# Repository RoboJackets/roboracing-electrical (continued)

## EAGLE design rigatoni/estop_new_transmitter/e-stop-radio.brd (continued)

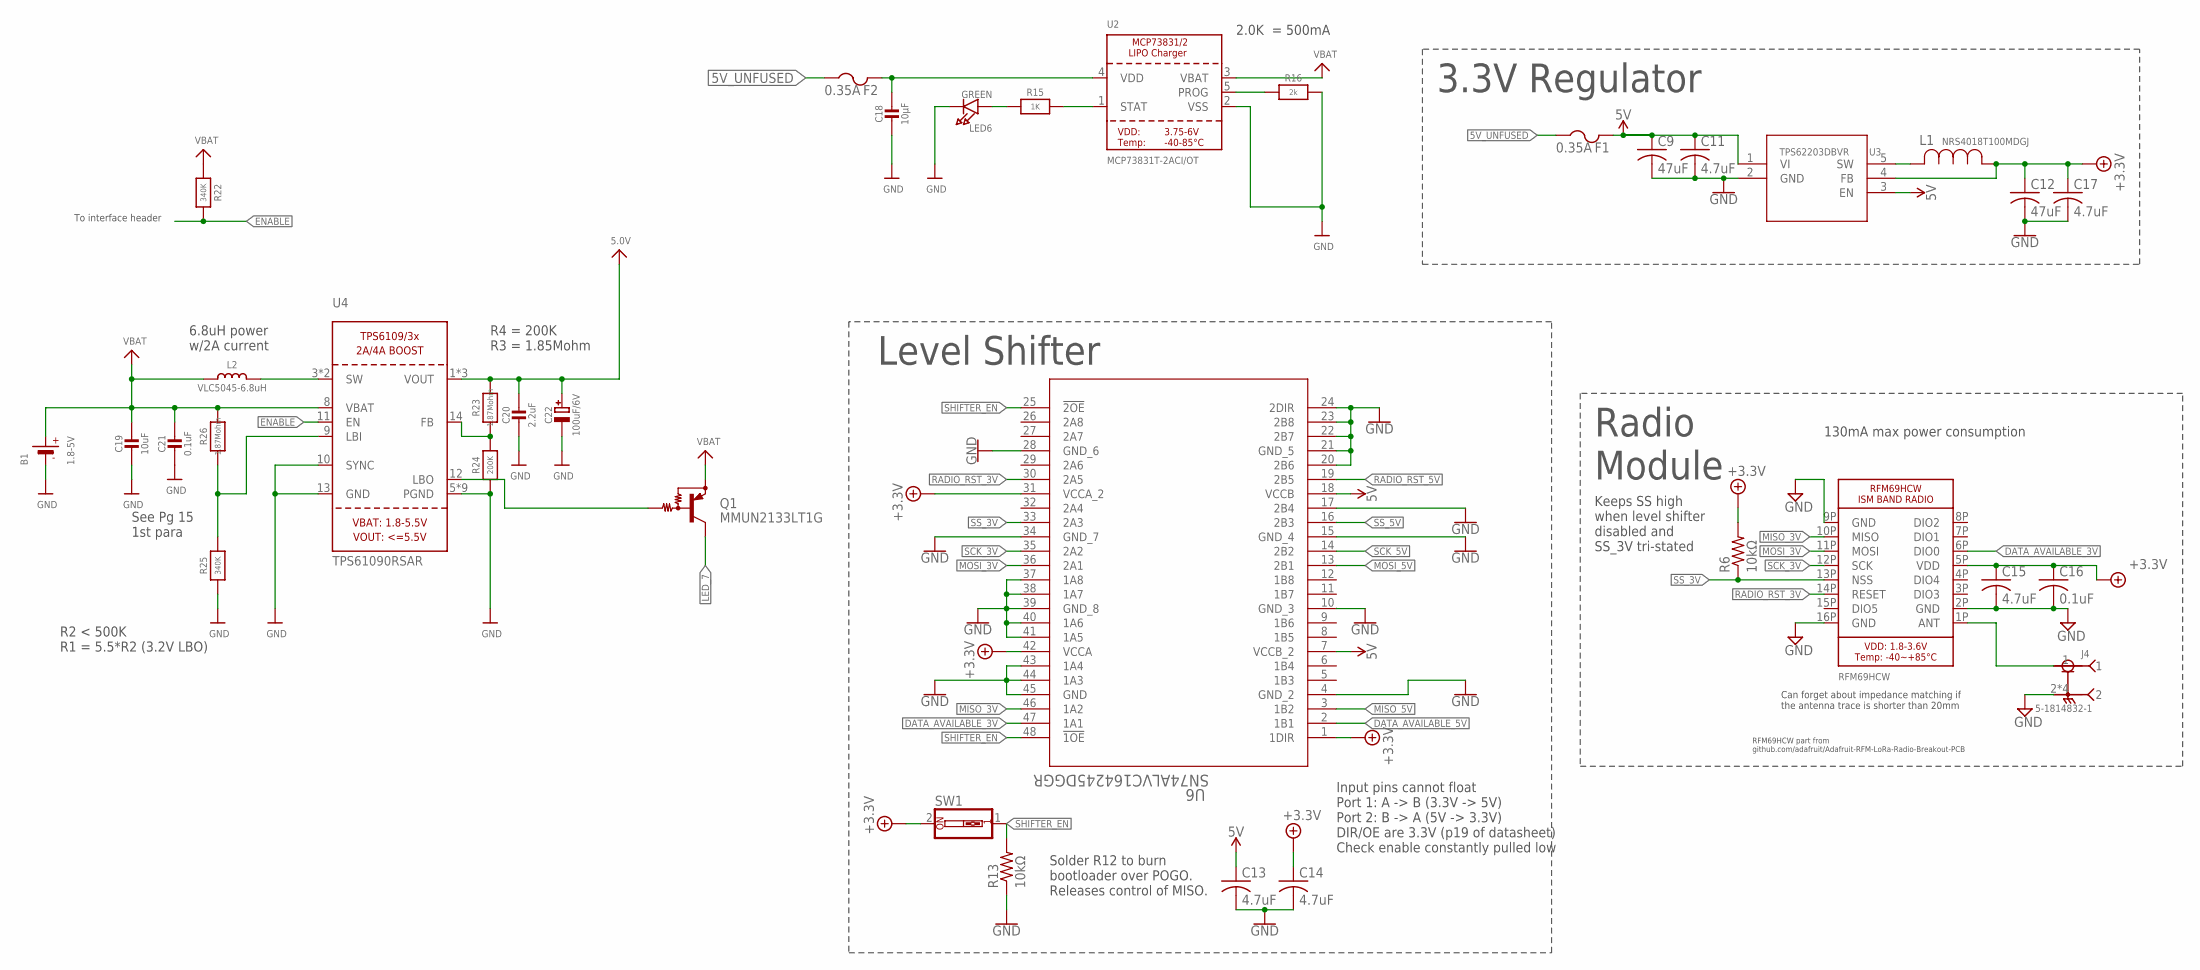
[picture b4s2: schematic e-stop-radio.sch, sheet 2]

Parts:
B1: 1.8-5V; JSTPH2
C9, C12: 47uF; C1206
C11, C13, C14, C15, C17: 4.7uF; C0603
C16: 0.1uF; C0603
C18: 10µF; 0805-NO
C19: 10uF; 0805-NO
C20: 2.2uF; 0805-NO
C21: 0.1uF; 0805-NO
C22: 100uF/6V; EIA3528-21/B-R
F1, F2: 0.35A; R1206
J4: 5-1814832-1; TE_5-1814832-1
L1: NRS4018T100MDGJ; IND_TAIYO_NRS4018
L2: VLC5045-6.8uH; INDUCTOR_5X5MM_TDK_VLC5045
LED6: GREEN; CHIPLED_0805_NOOUTLINE
Q1: MMUN2133LT1G; SC59-BEC
R6, R13: 10kΩ; R0603
R15: 1K; 0805-NO
R16: 2k; 0805-NO
R22, R25: 340K; 0805-NO
R23, R26: 1.87Mohm; 0805-NO
R24: 200K; 0805-NO
SW1: SW_DIP-1; EDG-01
U2: MCP73831T-2ACI/OT; SOT23-5
U3: TPS62203DBVR; DBV5
U4: TPS61090RSAR; PVQFN-16
U5: RFM69HCW; RFMHCW_SMT
U6: SN74ALVC164245DGGR; DGG48

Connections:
5V: C9.1, C11.1, C13.1, C20.1, C22.+, F1.2, R23.2, U3.1 (VI), U3.3 (EN), U4.1 (VOUT), U4.15 (VOUT), U4.16 (VOUT), U6.7 (VCCB_2), U6.18 (VCCB); also elsewhere on the board
5V_UNFUSED: F1.1, F2.1; also elsewhere on the board
+3.3V: C12.1, C14.1, C15.1, C16.1, C17.1, L1.1, R6.2, SW1.2, U3.4 (FB), U5.5P (VDD), U6.1 (1DIR), U6.31 (VCCA_2), U6.42 (VCCA); also elsewhere on the board
CHARGER: C18.1, F2.2, U2.4 (VDD)
DATA_AVAILABLE_3V: U5.6P (DIO0), U6.47 (1A1)
DATA_AVAILABLE_5V: U6.2 (1B1); also elsewhere on the board
ENABLE: R22.2, U4.11 (EN); also elsewhere on the board
GND: B1.1 (-), C9.2, C11.2, C12.2, C13.2, C14.2, C15.2, C16.2, C17.2, C18.2, C19.2, C20.2, C21.2, C22.-, J4.2, J4.3 (2), J4.4 (2), J4.5 (2), LED6.C, R13.1, R16.2, R24.1, R25.1, U2.2 (VSS), U3.2 (GND), U4.5 (PGND), U4.6 (PGND), U4.7 (PGND), U4.10 (SYNC), U4.13 (GND), U4.P$18 (PGND), U4.P$19 (PGND), U4.P$20 (PGND), U4.P$21 (PGND), U4.P$22 (PGND), U4.THERMAL (PGND), U5.2P (GND), U5.9P (GND), U5.16P (GND), U6.4 (GND_2), U6.10 (GND_3), U6.15 (GND_4), U6.17 (2B4), U6.20 (2B6), U6.21 (GND_5), U6.22 (2B7), U6.23 (2B8), U6.24 (2DIR), U6.28 (GND_6), U6.34 (GND_7), U6.37 (1A8), U6.38 (1A7), U6.39 (GND_8), U6.40 (1A6), U6.41 (1A5), U6.43 (1A4), U6.44 (1A3), U6.45 (GND); also elsewhere on the board
LBO: Q1.B, U4.12 (LBO)
LED_7: Q1.C; also elsewhere on the board
MISO_3V: U5.10P (MISO), U6.46 (1A2)
MISO_5V: U6.3 (1B2); also elsewhere on the board
MOSI_3V: U5.11P (MOSI), U6.36 (2A1)
MOSI_5V: U6.13 (2B1); also elsewhere on the board
unnamed: L1.2, U3.5 (SW)
unnamed: R15.2, U2.1 (STAT)
unnamed: R16.1, U2.5 (PROG)
unnamed: LED6.A, R15.1
unnamed: L2.P$2 (2), U4.3 (SW), U4.4 (SW)
unnamed: R25.2, R26.1, U4.9 (LBI)
unnamed: R23.1, R24.2, U4.14 (FB)
RADIO_RST_3V: U5.14P (RESET), U6.30 (2A5)
RADIO_RST_5V: U6.19 (2B5); also elsewhere on the board
RF_SIGNAL: J4.1, U5.1P (ANT)
SCK_3V: U5.12P (SCK), U6.35 (2A2)
SCK_5V: U6.14 (2B2); also elsewhere on the board
SHIFTER_EN: R13.2, SW1.1, U6.25 (!2OE), U6.48 (!1OE)
SS_3V: R6.1, U5.13P (NSS), U6.33 (2A3)
SS_5V: U6.16 (2B3); also elsewhere on the board
VBAT: B1.2 (+), C19.1, C21.1, L2.P$1 (1), Q1.E, R22.1, R26.2, U2.3 (VBAT), U4.8 (VBAT)

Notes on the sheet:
RFM69HCW part from github.com/adafruit/Adafruit-RFM-LoRa-Radio-Breakout-PCB
130mA max power consumption
Radio Module
Can forget about impedance matching if the antenna trace is shorter than 20mm
3.3V Regulator
Level Shifter
Solder R12 to burn bootloader over POGO. Releases control of MISO.
Input pins cannot float Port 1: A -> B (3.3V -> 5V) Port 2: B -> A (5V -> 3.3V) DIR/OE are 3.3V (p19 of datasheet) Check enable constantly pulled low
Keeps SS high when level shifter disabled and SS_3V tri-stated
2.0K = 500mA
See Pg 15 1st para
6.8uH power w/2A current
R2 < 500K R1 = 5.5*R2 (3.2V LBO)
R4 = 200K R3 = 1.85Mohm
To interface header

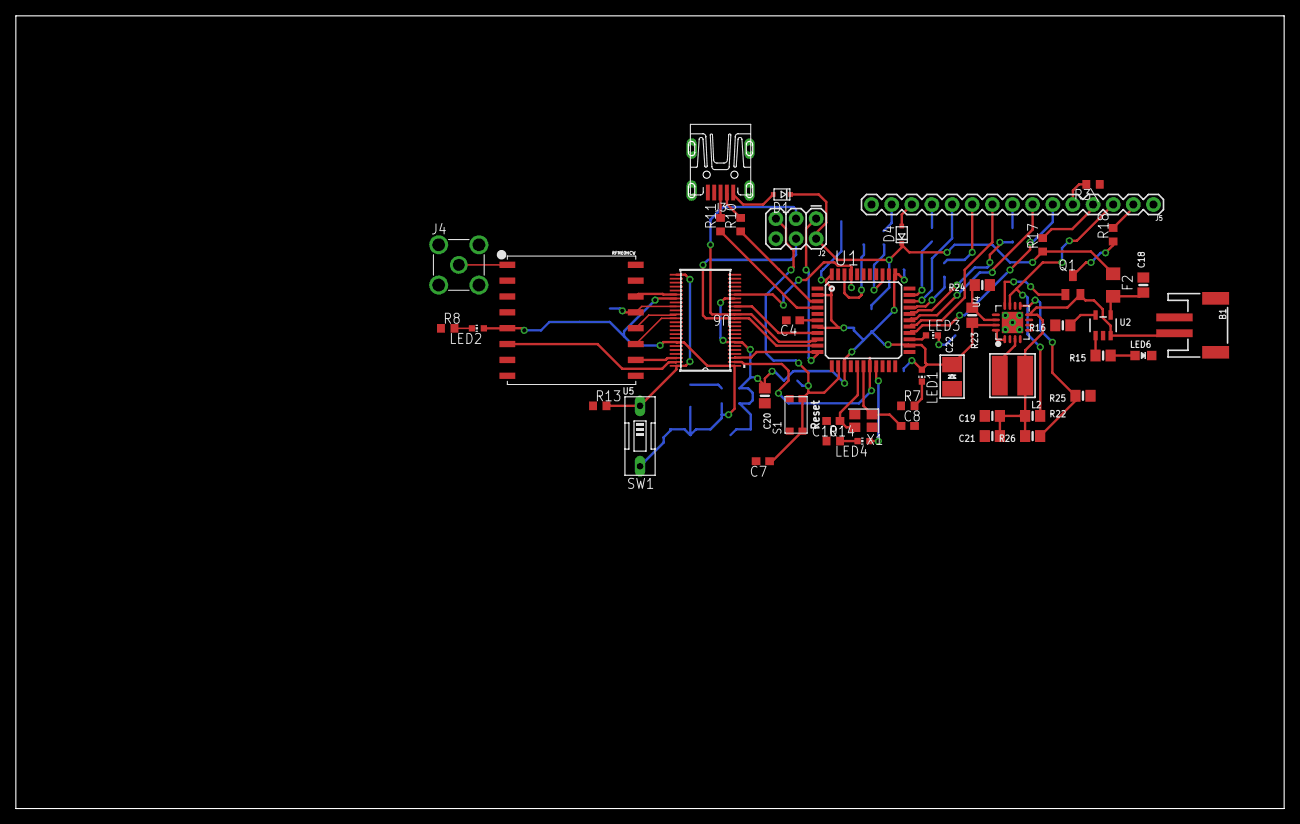
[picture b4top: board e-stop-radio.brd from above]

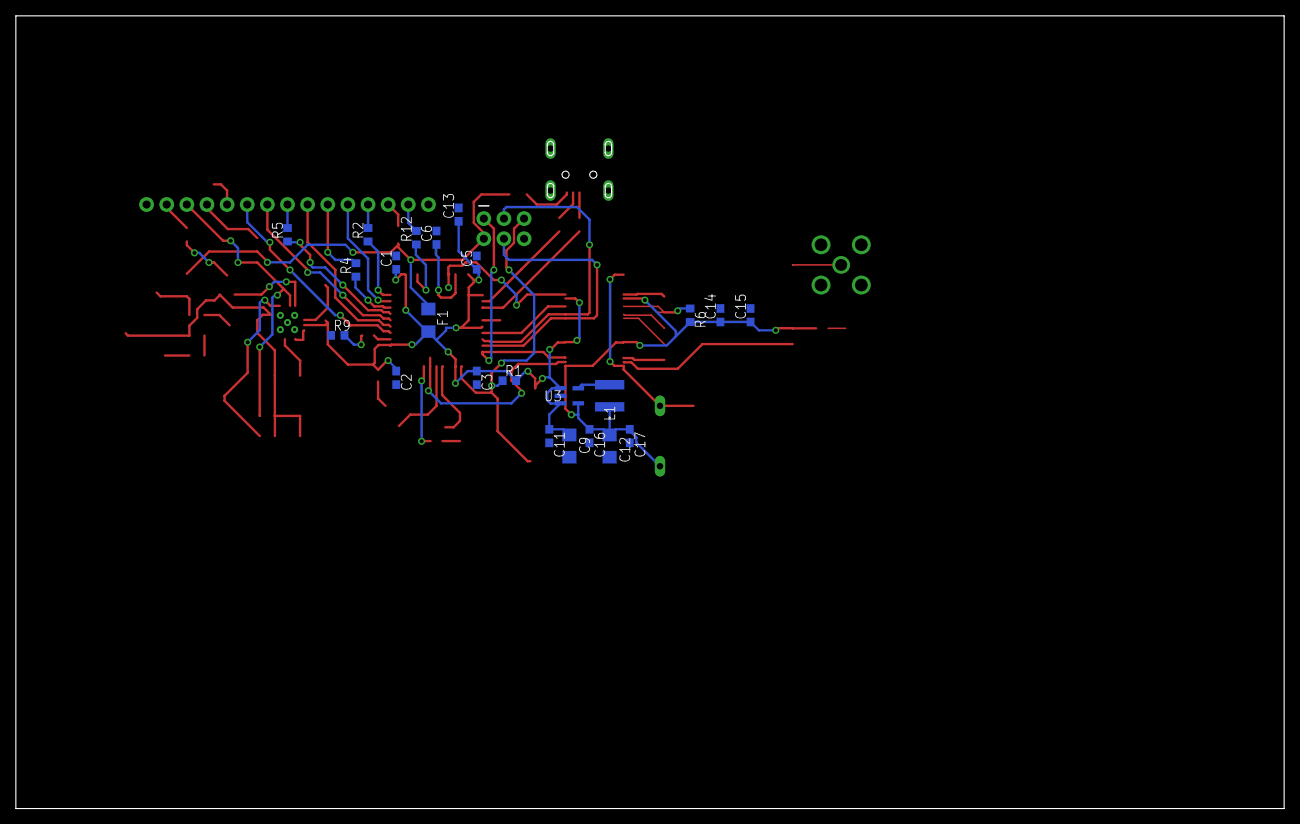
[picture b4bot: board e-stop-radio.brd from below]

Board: 2 copper layers, 160.0 x 100.0 mm, 71 parts (23 on the bottom side), 62 nets.

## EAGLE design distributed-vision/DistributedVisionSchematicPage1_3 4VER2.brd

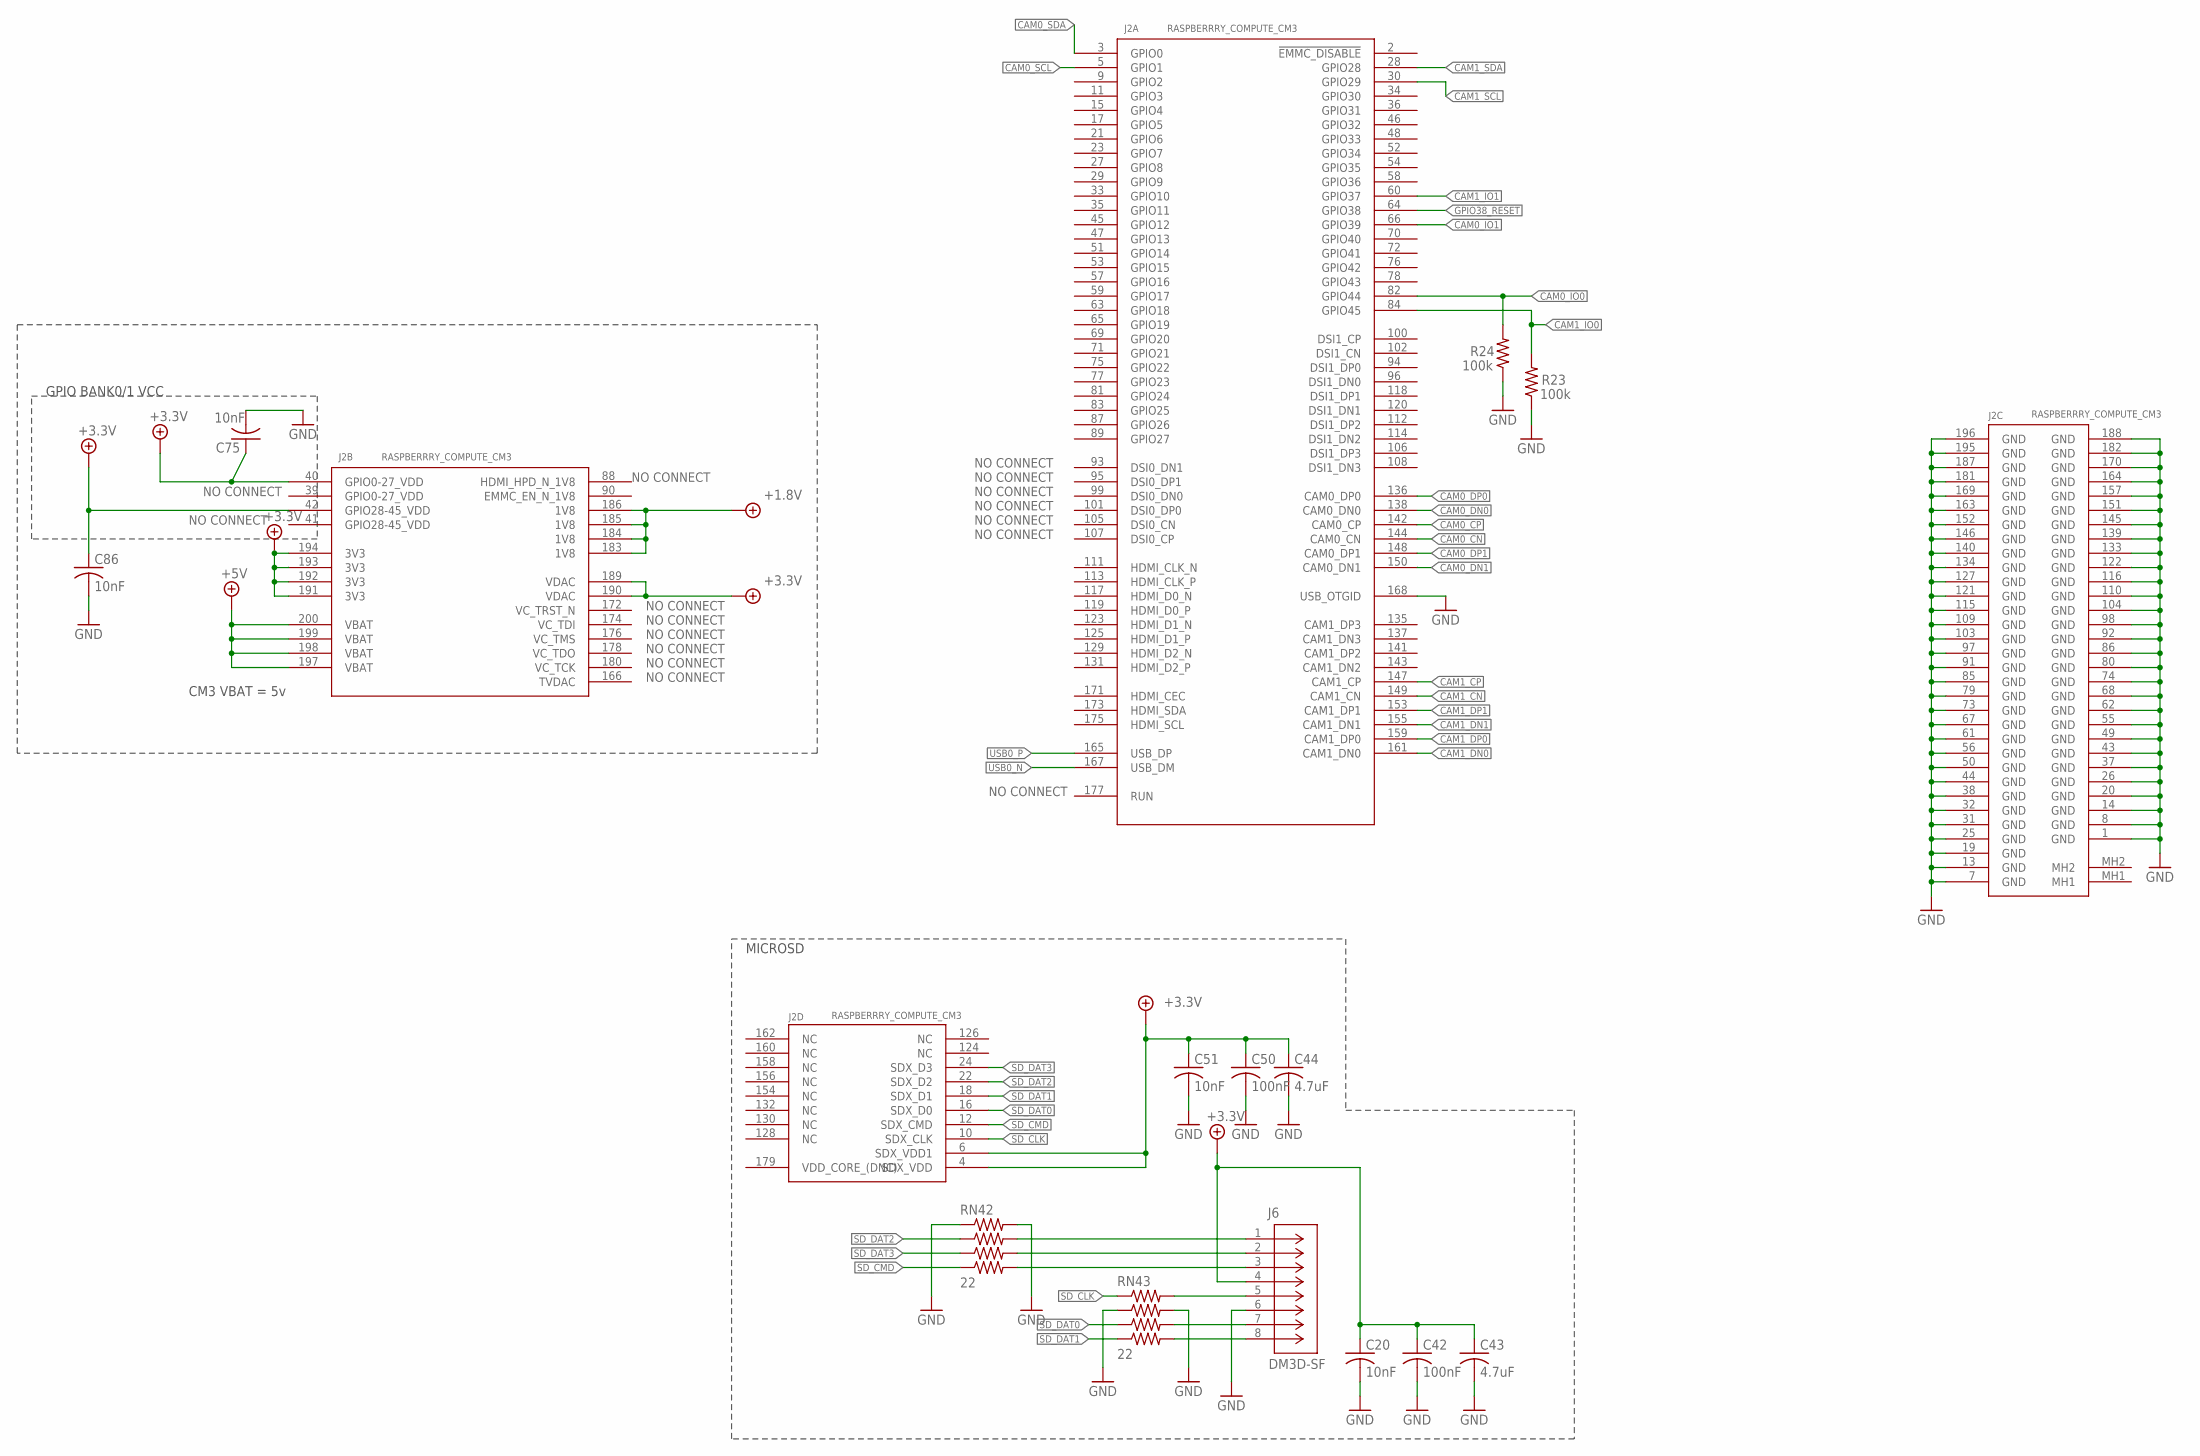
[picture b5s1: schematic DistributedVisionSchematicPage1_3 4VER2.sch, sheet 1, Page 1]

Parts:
C20, C51, C75, C86: 10nF; C0603
C42, C50: 100nF; C0603
C43, C44: 4.7uF; C0603
J2: RASPBERRRY_COMPUTE_CM3; TE_1473149-4_WITH_CM3PLUS
J6: DM3D-SF; CONN8_DM3D-SF_HIR
R23, R24: 100k; R0603
RN42, RN43: 22; RA-4_1206

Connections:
+1.8V: J2.183 (1V8), J2.184 (1V8), J2.185 (1V8), J2.186 (1V8); also elsewhere on the board
+3.3V: C20.1, C42.1, C43.1, C44.1, C50.1, C51.1, C75.1, C86.1, J2.4 (SDX_VDD), J2.6 (SDX_VDD1), J2.40 (GPIO0-27_VDD), J2.42 (GPIO28-45_VDD), J2.189 (VDAC), J2.190 (VDAC), J2.191 (3V3), J2.192 (3V3), J2.193 (3V3), J2.194 (3V3), J6.4; also elsewhere on the board
+5V: J2.197 (VBAT), J2.198 (VBAT), J2.199 (VBAT), J2.200 (VBAT); also elsewhere on the board
CAM0_CN: J2.144 (CAM0_CN); also elsewhere on the board
CAM0_CP: J2.142 (CAM0_CP); also elsewhere on the board
CAM0_DN0: J2.138 (CAM0_DN0); also elsewhere on the board
CAM0_DN1: J2.150 (CAM0_DN1); also elsewhere on the board
CAM0_DP0: J2.136 (CAM0_DP0); also elsewhere on the board
CAM0_DP1: J2.148 (CAM0_DP1); also elsewhere on the board
CAM0_IO0: J2.82 (GPIO44), R24.2; also elsewhere on the board
CAM0_IO1: J2.66 (GPIO39); also elsewhere on the board
CAM0_SCL: J2.5 (GPIO1); also elsewhere on the board
CAM0_SDA: J2.3 (GPIO0); also elsewhere on the board
CAM1_CN: J2.149 (CAM1_CN); also elsewhere on the board
CAM1_CP: J2.147 (CAM1_CP); also elsewhere on the board
CAM1_DN0: J2.161 (CAM1_DN0); also elsewhere on the board
CAM1_DN1: J2.155 (CAM1_DN1); also elsewhere on the board
CAM1_DP0: J2.159 (CAM1_DP0); also elsewhere on the board
CAM1_DP1: J2.153 (CAM1_DP1); also elsewhere on the board
CAM1_IO0: J2.84 (GPIO45), R23.2; also elsewhere on the board
CAM1_IO1: J2.60 (GPIO37); also elsewhere on the board
CAM1_SCL: J2.30 (GPIO29); also elsewhere on the board
CAM1_SDA: J2.28 (GPIO28); also elsewhere on the board
GND: C20.2, C42.2, C43.2, C44.2, C50.2, C51.2, C75.2, C86.2, J2.1 (GND), J2.7 (GND), J2.8 (GND), J2.13 (GND), J2.14 (GND), J2.19 (GND), J2.20 (GND), J2.25 (GND), J2.26 (GND), J2.31 (GND), J2.32 (GND), J2.37 (GND), J2.38 (GND), J2.43 (GND), J2.44 (GND), J2.49 (GND), J2.50 (GND), J2.55 (GND), J2.56 (GND), J2.61 (GND), J2.62 (GND), J2.67 (GND), J2.68 (GND), J2.73 (GND), J2.74 (GND), J2.79 (GND), J2.80 (GND), J2.85 (GND), J2.86 (GND), J2.91 (GND), J2.92 (GND), J2.97 (GND), J2.98 (GND), J2.103 (GND), J2.104 (GND), J2.109 (GND), J2.110 (GND), J2.115 (GND), J2.116 (GND), J2.121 (GND), J2.122 (GND), J2.127 (GND), J2.133 (GND), J2.134 (GND), J2.139 (GND), J2.140 (GND), J2.145 (GND), J2.146 (GND), J2.151 (GND), J2.152 (GND), J2.157 (GND), J2.163 (GND), J2.164 (GND), J2.168 (USB_OTGID), J2.169 (GND), J2.170 (GND), J2.181 (GND), J2.182 (GND), J2.187 (GND), J2.188 (GND), J2.195 (GND), J2.196 (GND), J6.6, R23.1, R24.1, RN42.1, RN42.2, RN43.3, RN43.4; also elsewhere on the board
GPIO0-27_VDD: J2.39 (GPIO0-27_VDD)
GPIO28-45_VDD: J2.41 (GPIO28-45_VDD)
GPIO38_RESET: J2.64 (GPIO38)
unnamed: J6.1, RN42.4
unnamed: J6.2, RN42.6
unnamed: J6.3, RN42.8
unnamed: J6.5, RN43.2
unnamed: J6.7, RN43.6
unnamed: J6.8, RN43.8
SD_CLK: J2.10 (SDX_CLK), RN43.1
SD_CMD: J2.12 (SDX_CMD), RN42.7
SD_DAT0: J2.16 (SDX_D0), RN43.5
SD_DAT1: J2.18 (SDX_D1), RN43.7
SD_DAT2: J2.22 (SDX_D2), RN42.3
SD_DAT3: J2.24 (SDX_D3), RN42.5
USB0_N: J2.167 (USB_DM); also elsewhere on the board
USB0_P: J2.165 (USB_DP); also elsewhere on the board
VC_TCK: J2.180 (VC_TCK)
VC_TDO: J2.178 (VC_TDO)

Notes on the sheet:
MICROSD
NO CONNECT
GPIO BANK0/1 VCC
CM3 VBAT = 5v

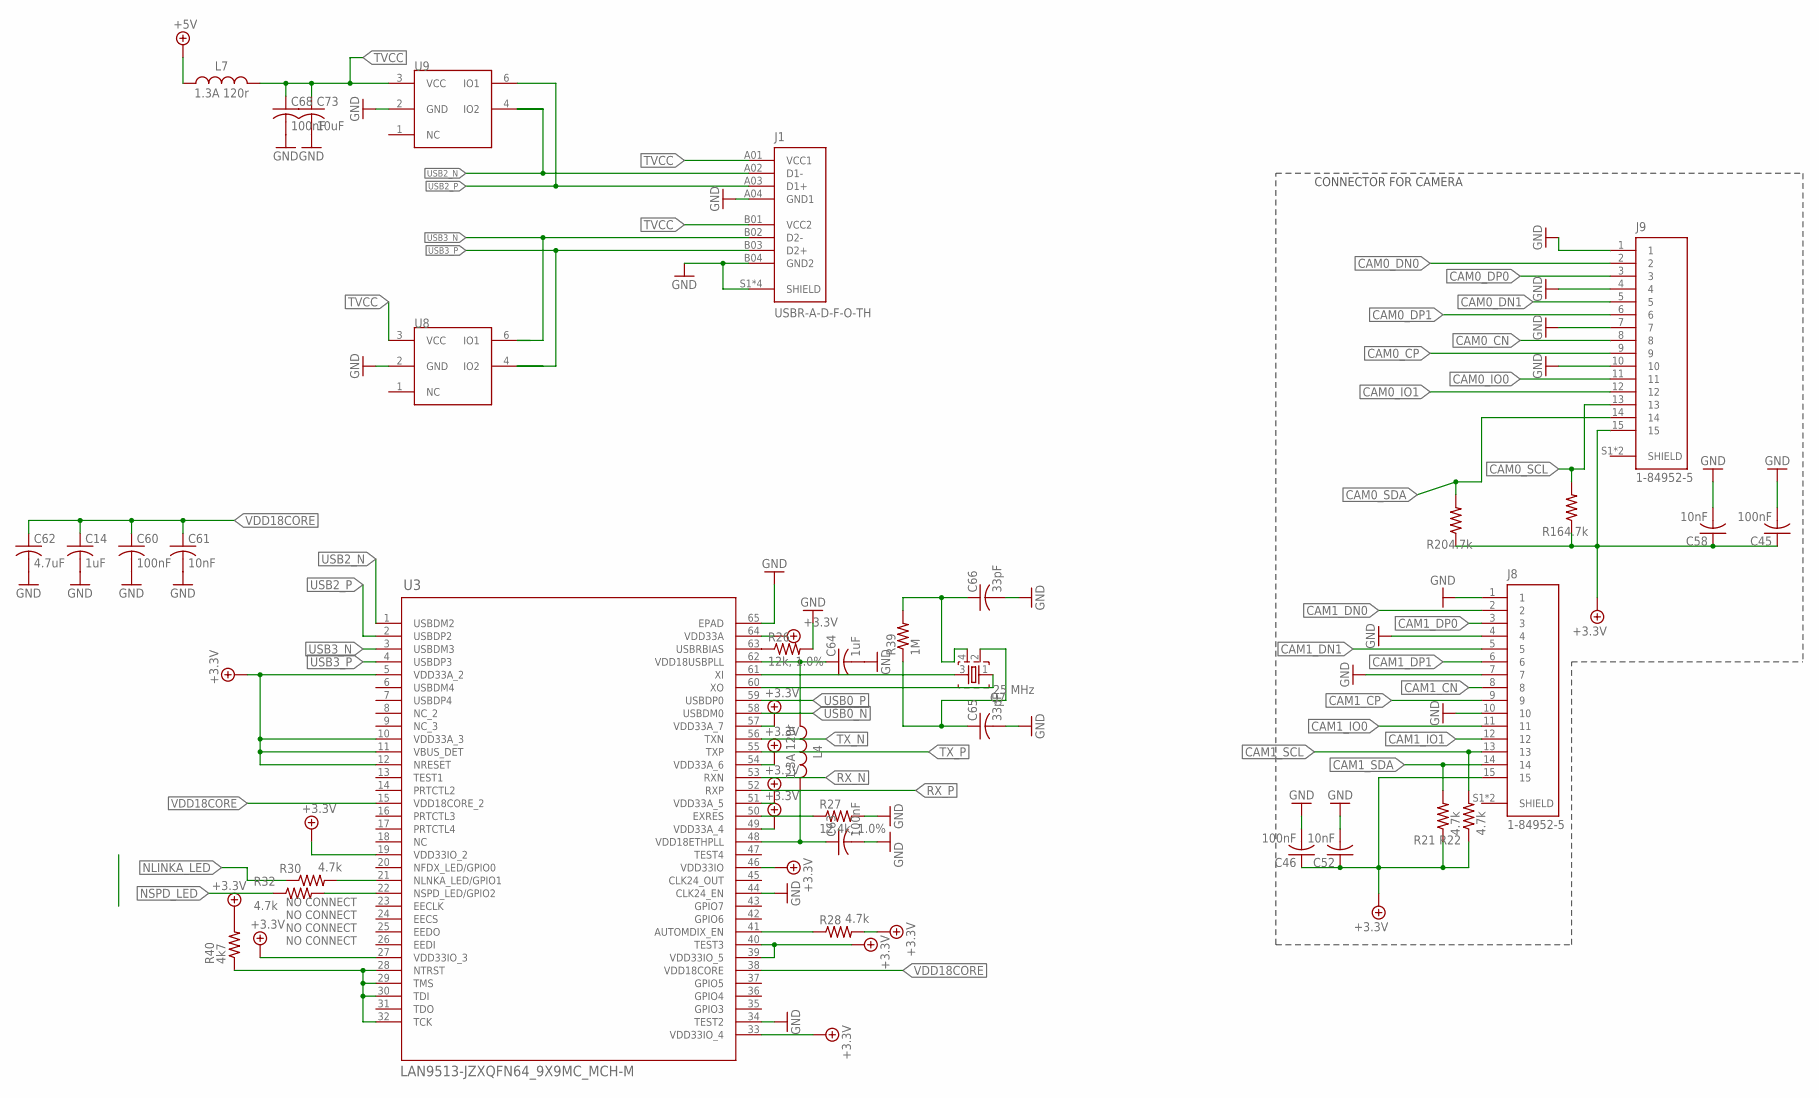
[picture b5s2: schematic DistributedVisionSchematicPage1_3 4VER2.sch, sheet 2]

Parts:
C14, C64: 1uF; C0402
C45, C46: 100nF; C0603
C52, C58: 10nF; C0603
C60, C63, C68: 100nF; C0402
C61: 10nF; C0402
C62: 4.7uF; C0402
C65, C66: 33pF; C0402
C73: 10uF; C0402
J1: USBR-A-D-F-O-TH; SAMTEC_USBR-A-D-F-O-TH
J8, J9: 1-84952-5; TE_1-84952-5
L4, L7: 1.3A 120r; 0805
Q7: 25 MHz; FA-20H
R16, R20, R21, R22: 4.7k; R0603
R26: 12k, 1.0%; RC0805N
R27: 12.4k, 1.0%; RC0805N
R28, R30, R32: 4.7k; RC0805N
R39: 1M; RC0805N
R40: 4k7; RC0805N
U3: LAN9513-JZXQFN64_9X9MC_MCH-M; QFN64_9X9MC_MCH-M
U8, U9: SP3003-02; SC70-5

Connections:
+3.3V: C45.1, C46.1, C52.1, C58.1, J8.15, J9.15, R16.1, R20.1, R21.1, R22.1, R28.2 (PIN2), R40.2 (PIN2), U3.5 (VDD33A_2), U3.10 (VDD33A_3), U3.11 (VBUS_DET), U3.12 (NRESET), U3.19 (VDD33IO_2), U3.27 (VDD33IO_3), U3.33 (VDD33IO_4), U3.39 (VDD33IO_5), U3.40 (TEST3), U3.46 (VDD33IO), U3.49 (VDD33A_4), U3.51 (VDD33A_5), U3.54 (VDD33A_6), U3.57 (VDD33A_7), U3.64 (VDD33A); also elsewhere on the board
+5V: L7.1; also elsewhere on the board
CAM0_CN: J9.8; also elsewhere on the board
CAM0_CP: J9.9; also elsewhere on the board
CAM0_DN0: J9.2; also elsewhere on the board
CAM0_DN1: J9.5; also elsewhere on the board
CAM0_DP0: J9.3; also elsewhere on the board
CAM0_DP1: J9.6; also elsewhere on the board
CAM0_IO0: J9.11; also elsewhere on the board
CAM0_IO1: J9.12; also elsewhere on the board
CAM0_SCL: J9.13, R16.2; also elsewhere on the board
CAM0_SDA: J9.14, R20.2; also elsewhere on the board
CAM1_CN: J8.8; also elsewhere on the board
CAM1_CP: J8.9; also elsewhere on the board
CAM1_DN0: J8.2; also elsewhere on the board
CAM1_DN1: J8.5; also elsewhere on the board
CAM1_DP0: J8.3; also elsewhere on the board
CAM1_DP1: J8.6; also elsewhere on the board
CAM1_IO0: J8.11; also elsewhere on the board
CAM1_IO1: J8.12; also elsewhere on the board
CAM1_SCL: J8.13, R22.2; also elsewhere on the board
CAM1_SDA: J8.14, R21.2; also elsewhere on the board
GND: C14.2, C45.2, C46.2, C52.2, C58.2, C60.2, C61.2, C62.2, C63.2, C64.2, C65.2, C66.2, C68.2, C73.2, J1.A04 (GND1), J1.B04 (GND2), J1.S1 (SHIELD), J1.S2 (SHIELD), J1.S3 (SHIELD), J1.S4 (SHIELD), J8.1, J8.4, J8.7, J8.10, J9.1, J9.4, J9.7, J9.10, R26.2 (PIN2), R27.2 (PIN2), U3.34 (TEST2), U3.44 (CLK24_EN), U3.65 (EPAD), U8.2 (GND), U9.2 (GND); also elsewhere on the board
unnamed: C64.1, L4.1, U3.62 (VDD18USBPLL)
unnamed: C63.1, L4.2, U3.48 (VDD18ETHPLL)
unnamed: R30.2 (PIN2), U3.21 (NLNKA_LED/GPIO1)
unnamed: R32.2 (PIN2), U3.22 (NSPD_LED/GPIO2)
unnamed: R40.1 (PIN1), U3.28 (NTRST), U3.29 (TMS), U3.30 (TDI), U3.32 (TCK)
unnamed: Q7.3, U3.61 (XI)
unnamed: Q7.1, U3.60 (XO)
unnamed: C66.1, Q7.4, R39.2 (PIN2)
unnamed: C65.1, Q7.2, R39.1 (PIN1)
unnamed: R26.1 (PIN1), U3.63 (USBRBIAS)
unnamed: R28.1 (PIN1), U3.41 (AUTOMDIX_EN)
unnamed: R27.1 (PIN1), U3.50 (EXRES)
NLINKA_LED: R30.1 (PIN1)
NSPD_LED: R32.1 (PIN1)
RX_N: U3.53 (RXN); also elsewhere on the board
RX_P: U3.52 (RXP); also elsewhere on the board
TVCC: C68.1, C73.1, J1.A01 (VCC1), J1.B01 (VCC2), L7.2, U8.3 (VCC), U9.3 (VCC)
TX_N: U3.56 (TXN); also elsewhere on the board
TX_P: U3.55 (TXP); also elsewhere on the board
USB0_N: U3.58 (USBDM0); also elsewhere on the board
USB0_P: U3.59 (USBDP0); also elsewhere on the board
USB2_N: J1.A02 (D1-), U3.1 (USBDM2)
USB2_P: J1.A03 (D1+), U3.2 (USBDP2)
USB3_N: J1.B02 (D2-), U3.3 (USBDM3)
USB3_P: J1.B03 (D2+), U3.4 (USBDP3)
USBDM2: U9.6 (IO1)
VDD18CORE: C14.1, C60.1, C61.1, C62.1, U3.15 (VDD18CORE_2), U3.38 (VDD18CORE)

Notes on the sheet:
CONNECTOR FOR CAMERA
NO CONNECT

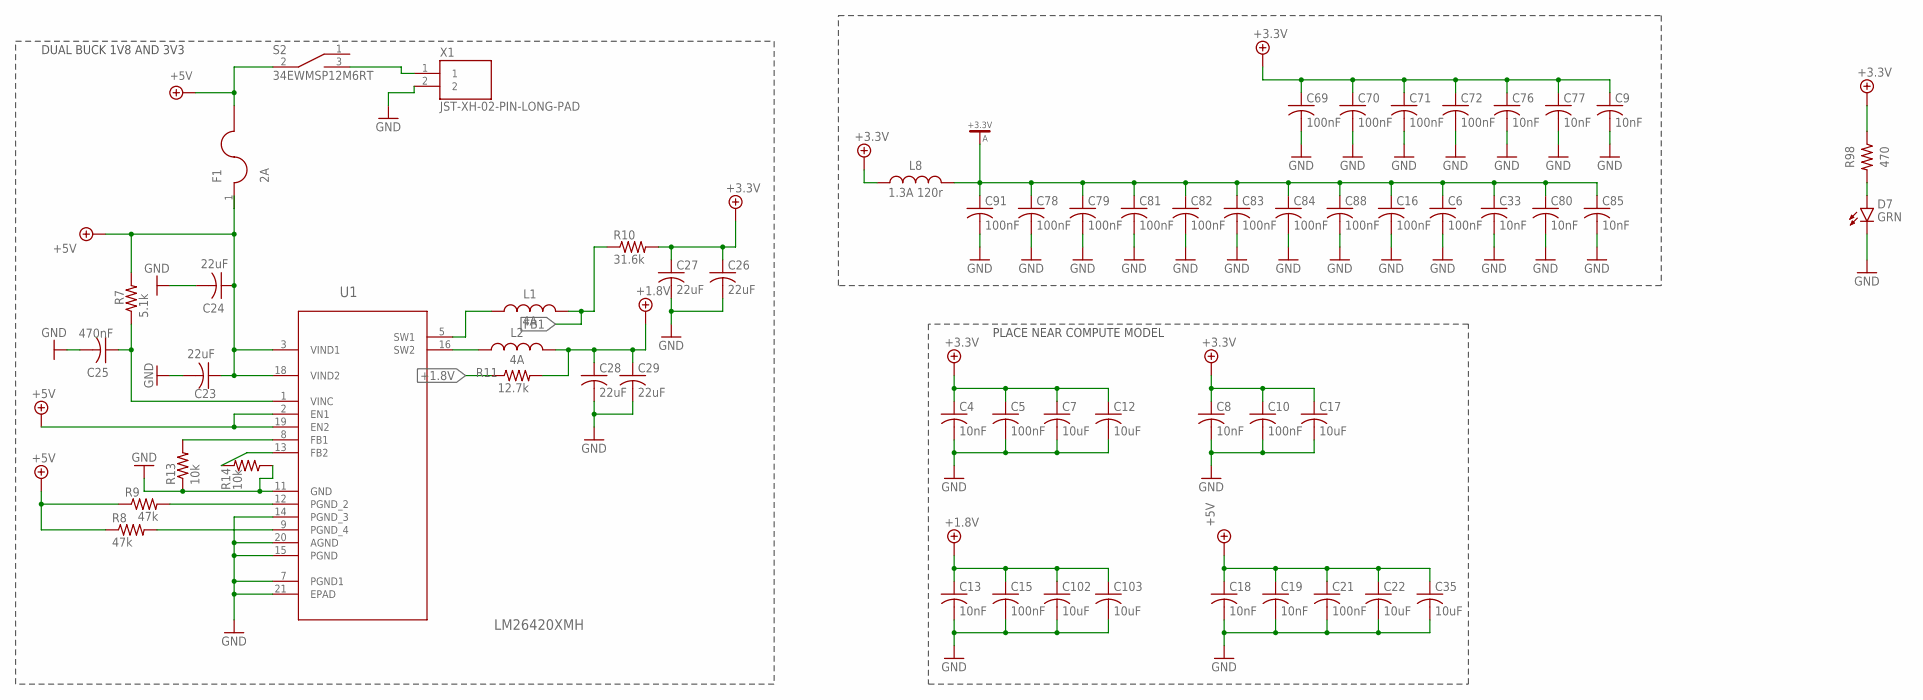
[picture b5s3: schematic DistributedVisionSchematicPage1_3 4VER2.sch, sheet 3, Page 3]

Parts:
C4, C8, C9, C13, C18, C19, C33, C76, C77, C80, C85: 10nF; C0603
C5, C6, C10, C15, C16, C21, C69, C70, C71, C72, C78, C79, C81, C82, C83, C84, C88, C91: 100nF; C0603
C7, C12, C17, C22, C35, C102, C103: 10uF; C0603
C23, C24: 22uF; C0603
C25: 470nF; C0603
C26, C27, C28, C29: 22uF; C0805
D7: GRN; CHIP-LED0603
F1: 2A; 1812
L1, L2: 4A; 0805
L8: 1.3A 120r; 0805
R7: 5.1k; R0603
R8, R9: 47k; R0603
R10: 31.6k; R0603
R11: 12.7k; R0603
R13, R14: 10k; R0603
R98: 470; R0603
S2: 34EWMSP12M6RT
U1: LM26420XMH; SOP65P640X175-21N
X1: JST-XH-02-PIN-LONG-PAD; JST-XH-02-PACKAGE-LONG-PAD

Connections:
3V3_LED: D7.A, R98.2
+1.8V: C13.1, C15.1, C28.1, C29.1, C102.1, C103.1, L2.2, R11.2; also elsewhere on the board
+3.3V: C4.1, C5.1, C7.1, C8.1, C9.1, C10.1, C12.1, C17.1, C26.1, C27.1, C69.1, C70.1, C71.1, C72.1, C76.1, C77.1, L8.1, R10.2, R98.1; also elsewhere on the board
+3.3V-A: C6.1, C16.1, C33.1, C78.1, C79.1, C80.1, C81.1, C82.1, C83.1, C84.1, C85.1, C88.1, C91.1, L8.2
+5V: C18.1, C19.1, C21.1, C22.1, C23.1, C24.1, C35.1, F1.1, F1.2, R7.2, R8.1, R9.1, S2.2 (COMMON), U1.2 (EN1), U1.3 (VIND1), U1.18 (VIND2), U1.19 (EN2); also elsewhere on the board
BVCC: S2.3 (B), X1.1
FB1: L1.2, R10.1
GND: C4.2, C5.2, C6.2, C7.2, C8.2, C9.2, C10.2, C12.2, C13.2, C15.2, C16.2, C17.2, C18.2, C19.2, C21.2, C22.2, C23.2, C24.2, C25.2, C26.2, C27.2, C28.2, C29.2, C33.2, C35.2, C69.2, C70.2, C71.2, C72.2, C76.2, C77.2, C78.2, C79.2, C80.2, C81.2, C82.2, C83.2, C84.2, C85.2, C88.2, C91.2, C102.2, C103.2, D7.C, R13.1, R14.1, U1.7 (PGND1), U1.11 (GND), U1.14 (PGND_3), U1.15 (PGND), U1.20 (AGND), U1.21 (EPAD), X1.2; also elsewhere on the board
unnamed: R13.2, U1.8 (FB1)
unnamed: C25.1, R7.1, U1.1 (VINC)
unnamed: R8.2, U1.9 (PGND_4)
RX_N: L1.1, U1.5 (SW1); also elsewhere on the board
RX_P1: R9.2, U1.12 (PGND_2)
USBDM4: L2.1, U1.16 (SW2)
USBDP4: R14.2, U1.13 (FB2)

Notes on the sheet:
DUAL BUCK 1V8 AND 3V3
PLACE NEAR COMPUTE MODEL

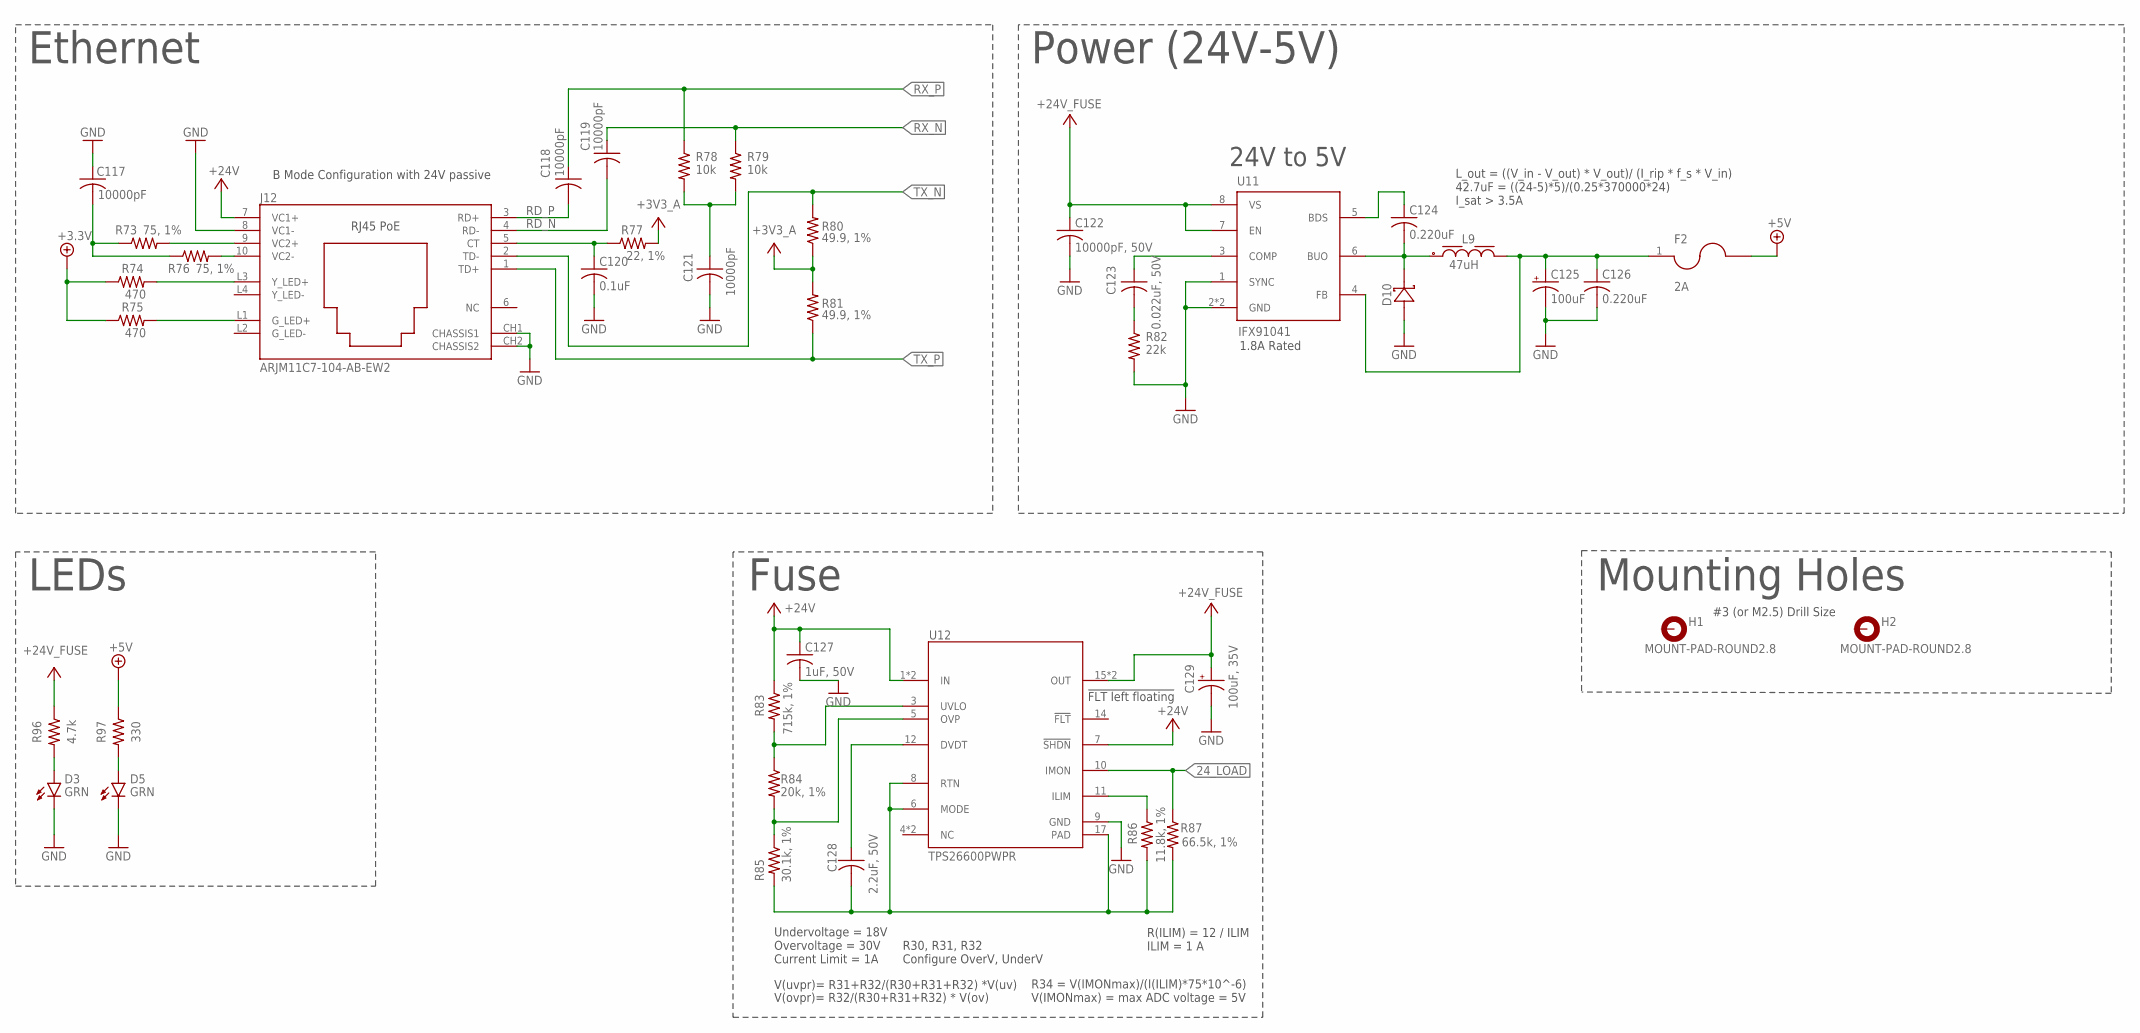
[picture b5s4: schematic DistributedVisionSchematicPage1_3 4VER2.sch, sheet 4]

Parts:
C117, C121: 10000pF; C0603
C118, C119: 10000pF; C0402
C120: 0.1uF; C0402
C122: 10000pF, 50V; C0603
C123: 0.022uF, 50V; C0603
C124, C126: 0.220uF; C0603
C125: 100uF; E2-5
C127: 1uF, 50V; C0603
C128: 2.2uF, 50V; C0603
C129: 100uF, 35V; E2,5-7
D3, D5: GRN; CHIP-LED0603
D10: NTS260ESFT3G; SOD123FL_DIO
F2: 2A; 1812
H1, H2: MOUNT-PAD-ROUND2.8; 2,8-PAD
J12: ARJM11C7-104-AB-EW2; CONN_EW_ABR
L9: 47uH; WE-PD_1210
R73, R76: 75, 1%; R0603
R74, R75: 470; R0603
R77: 22, 1%; R0603
R78, R79: 10k; R0603
R80, R81: 49.9, 1%; R0402
R82: 22k; R0603
R83: 715k, 1%; R0603
R84: 20k, 1%; R0603
R85: 30.1k, 1%; R0603
R86: 11.8k, 1%; R0603
R87: 66.5k, 1%; R0603
R96: 4.7k; R0603
R97: 330; R0603
U11: IFX91041; SOIC-8-EXPOSED_PAD
U12: TPS26600PWPR; PWP0016H_N

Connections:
5V_LED: D5.A, R97.2
5V_RAW: C124.2, D10.1, L9.1, U11.6 (BUO)
24V_LED: D3.A, R96.2
24_LOAD: R87.1, U12.10 (IMON)
+3.3V: R74.1, R75.1; also elsewhere on the board
+3V3_A: R77.2, R80.1, R81.2
+5V: F2.2, R97.1; also elsewhere on the board
+5V_PREFUSE: C125.+, C126.1, F2.1, L9.2, U11.4 (FB)
+24V: C127.1, J12.7 (VC1+), R83.1, U12.1 (IN), U12.2 (IN), U12.7 (!SHDN)
+24V_FUSE: C122.1, C129.+, R96.1, U11.7 (EN), U11.8 (VS), U12.15 (OUT), U12.16 (OUT)
CT: C120.1, J12.5 (CT), R77.1
GND: C117.1, C120.2, C121.2, C122.2, C125.-, C126.2, C127.2, C129.-, D3.C, D5.C, D10.2, J12.8 (VC1-), J12.CH1 (CHASSIS1), J12.CH2 (CHASSIS2), R82.2, U11.1 (SYNC), U11.2 (GND), U11.9 (GND), U12.9 (GND); also elsewhere on the board
G_LED+: J12.L1 (G_LED+), R75.2
unnamed: C123.1, U11.3 (COMP)
unnamed: J12.9 (VC2+), R73.2
unnamed: J12.10 (VC2-), R76.2
unnamed: C124.1, U11.5 (BDS)
unnamed: C123.2, R82.1
unnamed: C117.2, R73.1, R76.1
unnamed: R83.2, R84.1, U12.3 (UVLO)
unnamed: R84.2, R85.1, U12.5 (OVP)
unnamed: C128.1, U12.12 (DVDT)
unnamed: R86.1, U12.11 (ILIM)
RD_N: C119.2, J12.4 (RD-)
RD_P: C118.2, J12.3 (RD+)
RTN: C128.2, R85.2, R86.2, R87.2, U12.6 (MODE), U12.8 (RTN), U12.17 (PAD)
RX_FILTER: C121.1, R78.2, R79.2
RX_N: C119.1, R79.1; also elsewhere on the board
RX_P: C118.1, R78.1; also elsewhere on the board
TX_N: J12.2 (TD-), R80.2; also elsewhere on the board
TX_P: J12.1 (TD+), R81.1; also elsewhere on the board
Y_LED+: J12.L3 (Y_LED+), R74.2

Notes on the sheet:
Power (24V-5V)
LEDs
Ethernet
24V to 5V
B Mode Configuration with 24V passive
R(ILIM) = 12 / ILIM ILIM = 1 A
Undervoltage = 18V Overvoltage = 30V Current Limit = 1A
R30, R31, R32 Configure OverV, UnderV
V(ovpr)= R32/(R30+R31+R32) * V(ov)
V(uvpr)= R31+R32/(R30+R31+R32) *V(uv)
Fuse
!FLT left floating
Mounting Holes
R34 = V(IMONmax)/(I(ILIM)*75*10^-6) V(IMONmax) = max ADC voltage = 5V
1.8A Rated
#3 (or M2.5) Drill Size
L_out = ((V_in - V_out) * V_out)/ (I_rip * f_s * V_in) 42.7uF = ((24-5)*5)/(0.25*370000*24) I_sat > 3.5A
